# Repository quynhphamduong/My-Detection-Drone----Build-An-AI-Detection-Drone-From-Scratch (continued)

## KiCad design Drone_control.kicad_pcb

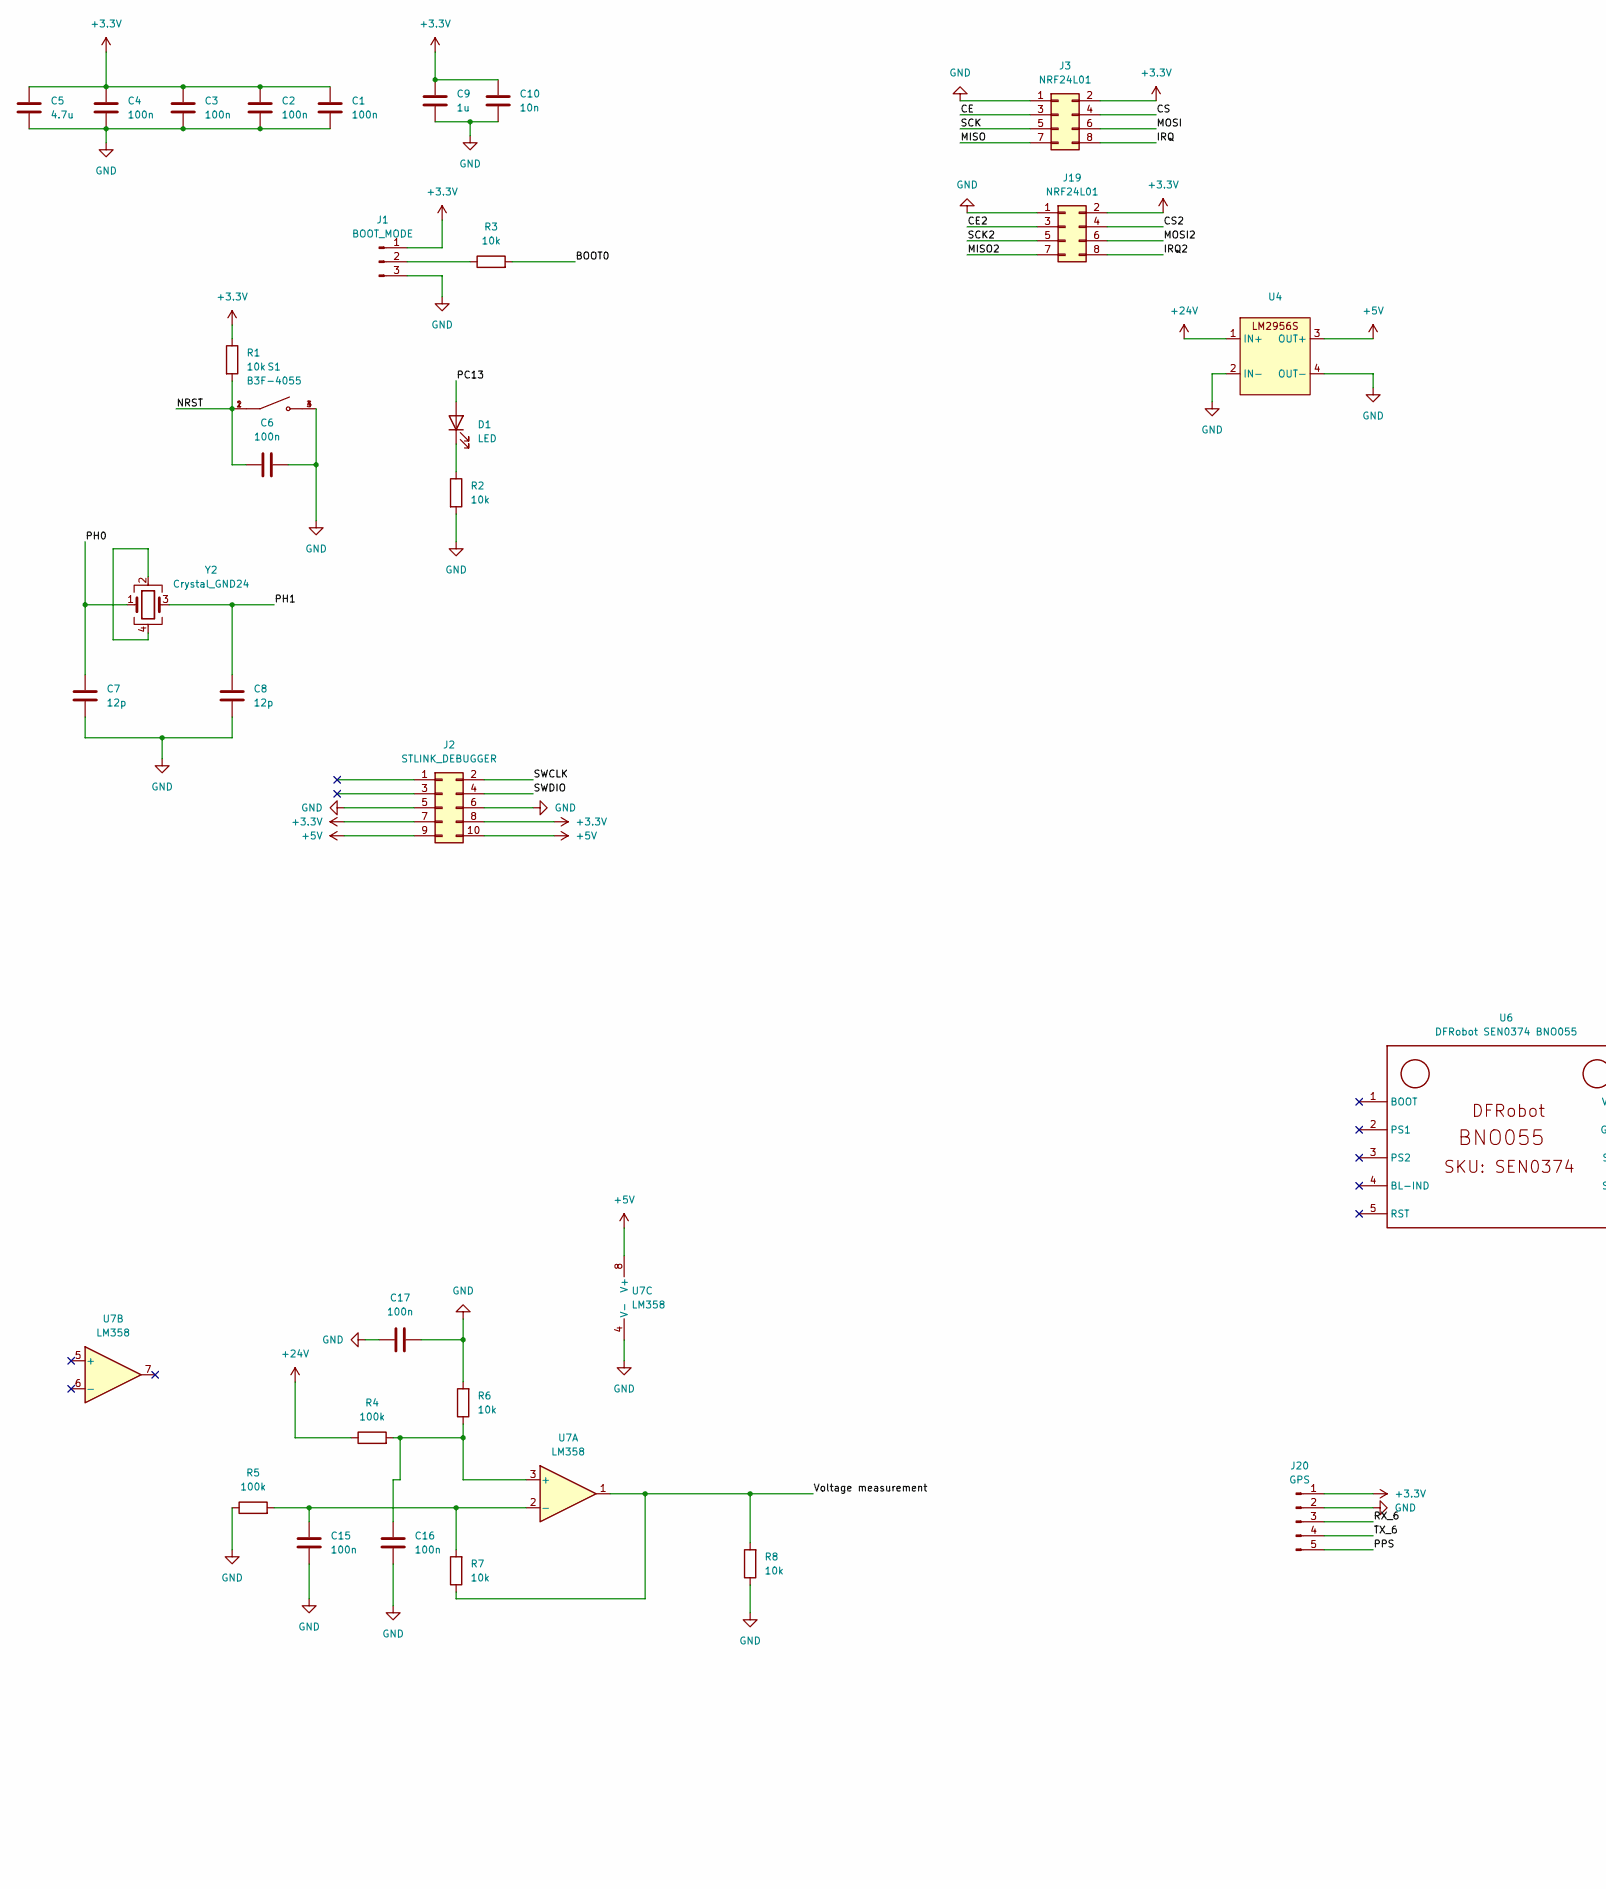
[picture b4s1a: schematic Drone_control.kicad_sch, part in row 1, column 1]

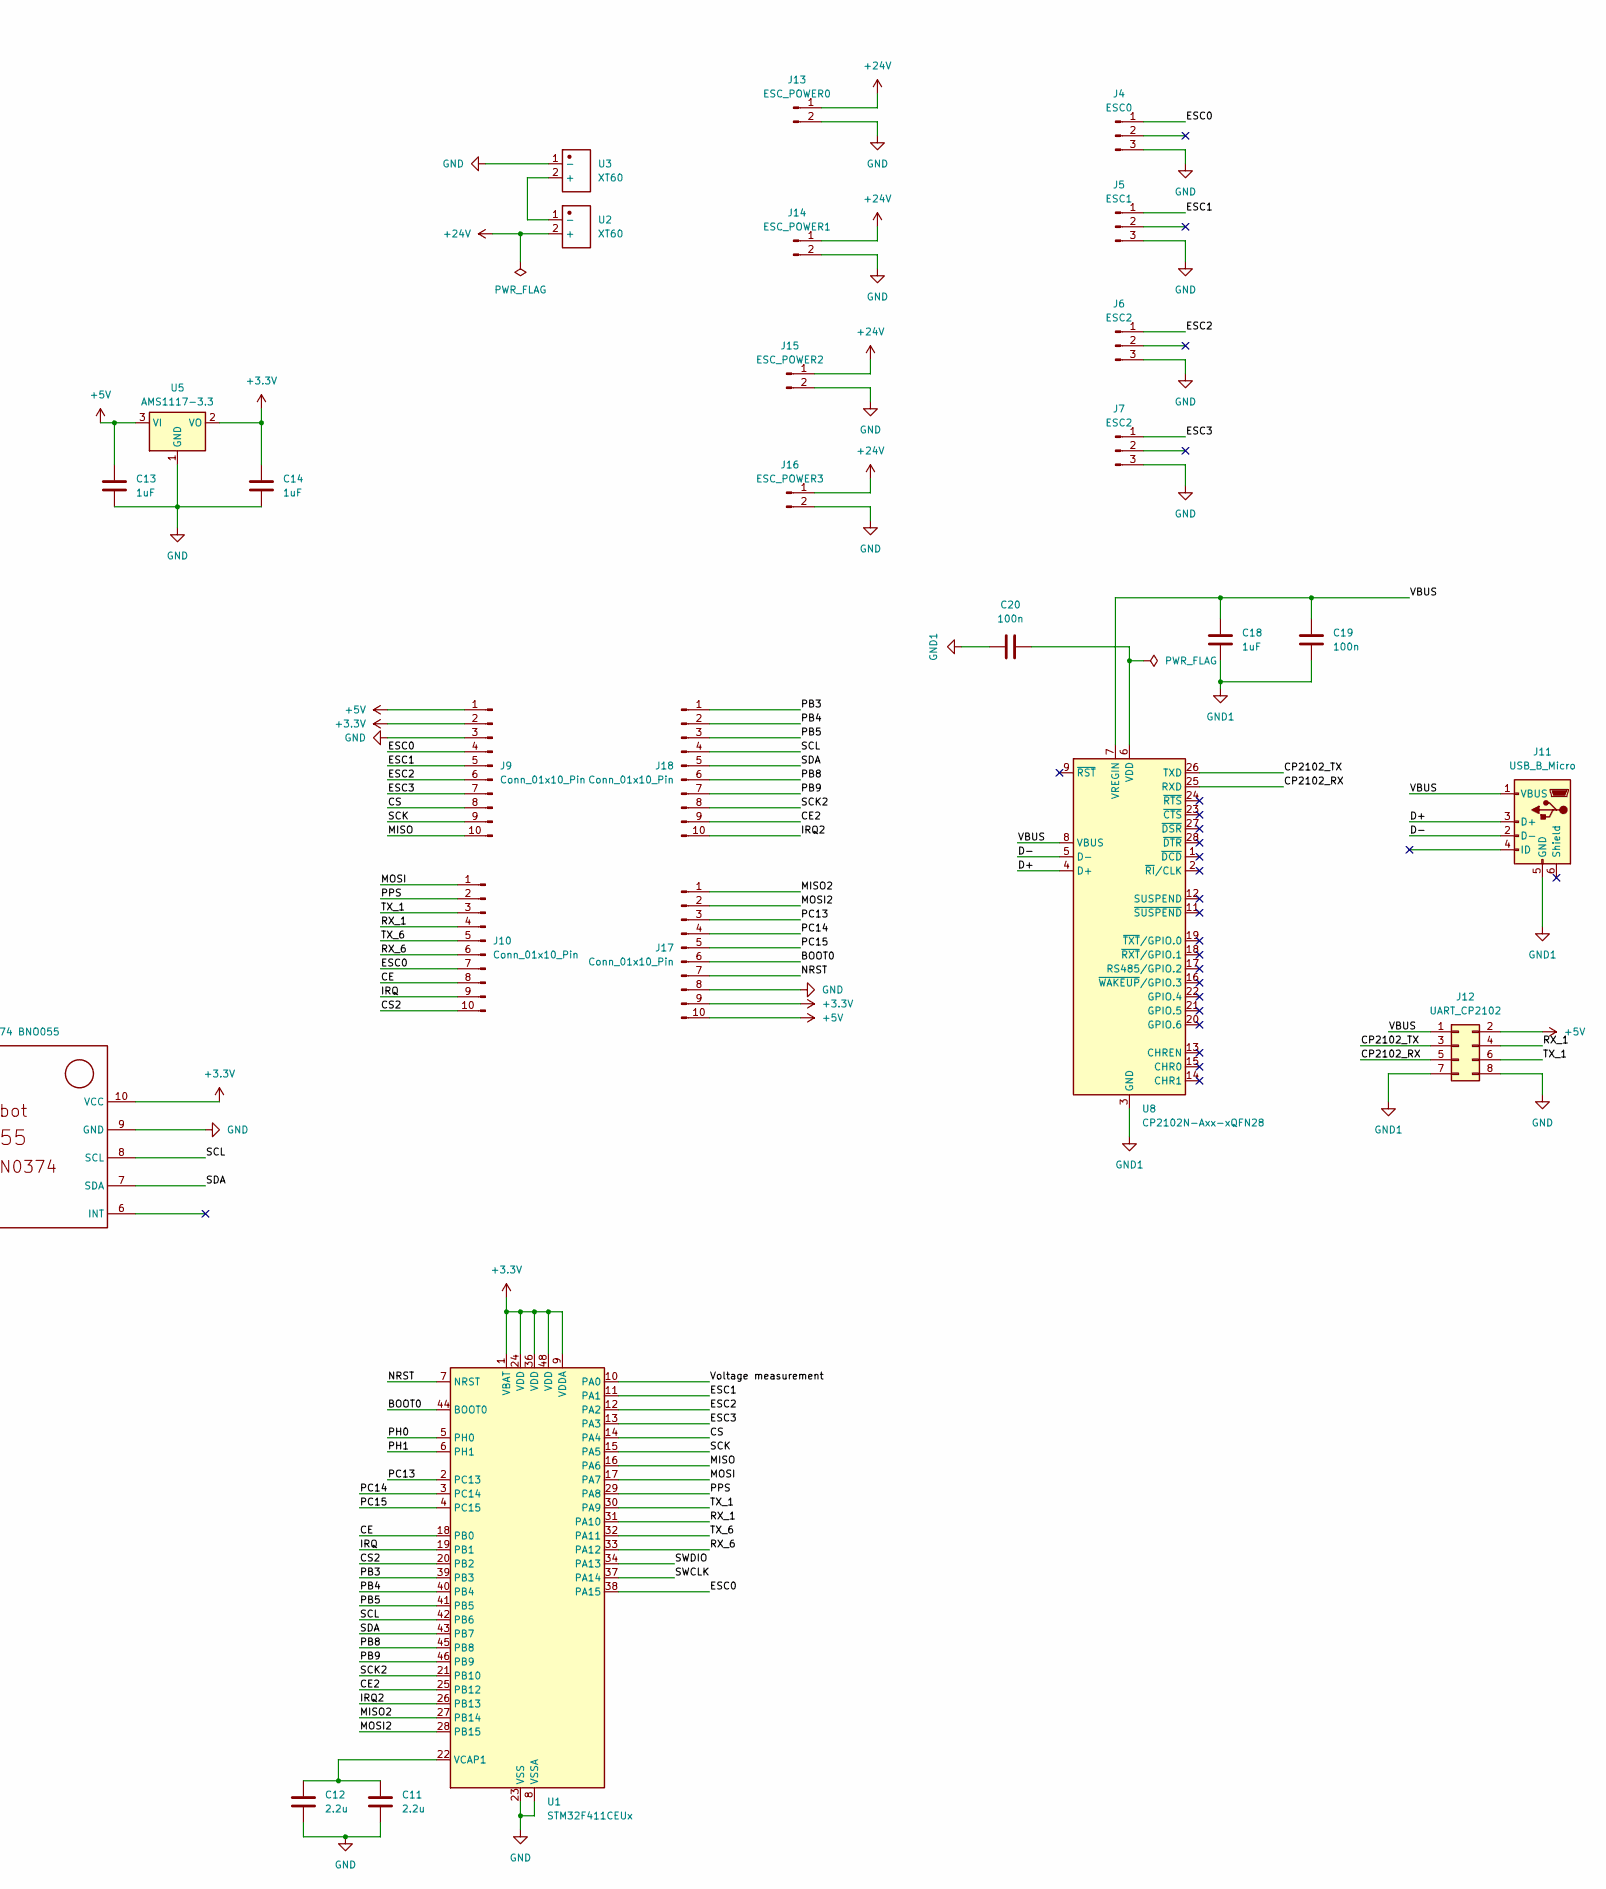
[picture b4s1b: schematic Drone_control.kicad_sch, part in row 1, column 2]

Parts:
C1, C2, C3, C4, C6, C15, C16, C17, C19, C20: 100n; C_0805_2012Metric_Pad1.18x1.45mm_HandSolder
C5: 4.7u; C_0805_2012Metric_Pad1.18x1.45mm_HandSolder
C7, C8: 12p; C_0805_2012Metric_Pad1.18x1.45mm_HandSolder
C9: 1u; C_0805_2012Metric_Pad1.18x1.45mm_HandSolder
C10: 10n; C_0805_2012Metric_Pad1.18x1.45mm_HandSolder
C11, C12: 2.2u; C_0805_2012Metric_Pad1.18x1.45mm_HandSolder
C13, C14, C18: 1uF; C_0805_2012Metric_Pad1.18x1.45mm_HandSolder
D1: LED; LED_0805_2012Metric_Pad1.15x1.40mm_HandSolder
J1: BOOT_MODE; PinHeader_1x03_P2.54mm_Vertical
J2: STLINK_DEBUGGER; IDC-Header_2x05_P2.54mm_Vertical
J3, J19: NRF24L01; PinHeader_2x04_P2.54mm_Vertical
J4: ESC0; PinHeader_1x03_P2.54mm_Vertical
J5: ESC1; PinHeader_1x03_P2.54mm_Vertical
J6, J7: ESC2; PinHeader_1x03_P2.54mm_Vertical
J9, J10, J17, J18: Conn_01x10_Pin; PinHeader_1x10_P2.54mm_Vertical
J11: USB_B_Micro; USB_Micro-B_Amphenol_10104110_Horizontal
J12: UART_CP2102; PinHeader_2x04_P2.54mm_Vertical
J13: ESC_POWER0; ESC_Power_Pad
J14: ESC_POWER1; ESC_Power_Pad
J15: ESC_POWER2; ESC_Power_Pad
J16: ESC_POWER3; ESC_Power_Pad
J20: GPS; PinHeader_1x05_P2.54mm_Vertical
R1, R2, R3, R6, R7, R8: 10k; R_0805_2012Metric_Pad1.20x1.40mm_HandSolder
R4, R5: 100k; R_0805_2012Metric_Pad1.20x1.40mm_HandSolder
S1: B3F-4055; SW_B3F-4055; PARTREV A070-E1-08
U1: STM32F411CEUx; QFN-48-1EP_7x7mm_P0.5mm_EP5.6x5.6mm
U2, U3: XT60; AMASS_XT60-M_1x02_P7.20mm_Vertical; Manufacturer Part XT60
U4: LM2596_Module
U5: AMS1117-3.3; SOT-223-3_TabPin2
U6: DFRobot SEN0374 BNO055; FOOTPRINT DFROBOT SEN0374 BNO055
U7: LM358; DIP-8_W7.62mm_Socket
U8: CP2102N-Axx-xQFN28; QFN-28-1EP_5x5mm_P0.5mm_EP3.35x3.35mm
Y2: Crystal_GND24; Crystal_SMD_5032-4Pin_5.0x3.2mm

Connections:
+3.3V: C1.1, C2.1, C3.1, C4.1, C5.1, C9.1, C10.1, C14.2, J1.1, J2.7, J2.8, J3.2, J9.2, J17.9, J19.2, J20.1, R1.1, U1.1 (VBAT), U1.9 (VDDA), U1.24 (VDD), U1.36 (VDD), U1.48 (VDD), U5.2 (VO), U6.10 (VCC)
+5V: C13.2, J2.9, J2.10, J9.1, J12.2, J17.10, U4.3 (OUT+), U5.3 (VI), U7.8 (V+)
+24V: J13.1, J14.1, J15.1, J16.1, R4.1, U2.2 (+), U4.1 (IN+)
/BOOT0: J17.6, R3.2, U1.44 (BOOT0)
/CE: J3.3, J10.8, U1.18 (PB0)
/CE2: J18.9, J19.3, U1.25 (PB12)
/CP2102_RX: J12.5, U8.25 (RXD)
/CP2102_TX: J12.3, U8.26 (TXD)
/CS: J3.4, J9.8, U1.14 (PA4)
/CS2: J10.10, J19.4, U1.20 (PB2)
/D+: J11.3 (D+), U8.4 (D+)
/D-: J11.2 (D-), U8.5 (D-)
/ESC0: J4.1, J9.4, J10.7, U1.38 (PA15)
/ESC1: J5.1, J9.5, U1.11 (PA1)
/ESC2: J6.1, J9.6, U1.12 (PA2)
/ESC3: J7.1, J9.7, U1.13 (PA3)
/IRQ: J3.8, J10.9, U1.19 (PB1)
/IRQ2: J18.10, J19.8, U1.26 (PB13)
/MISO: J3.7, J9.10, U1.16 (PA6)
/MISO2: J17.1, J19.7, U1.27 (PB14)
/MOSI: J3.6, J10.1, U1.17 (PA7)
/MOSI2: J17.2, J19.6, U1.28 (PB15)
/NRST: C6.1, J17.7, R1.2, S1.1, S1.2, U1.7 (NRST)
/PB3: J18.1, U1.39 (PB3)
/PB4: J18.2, U1.40 (PB4)
/PB5: J18.3, U1.41 (PB5)
/PB8: J18.6, U1.45 (PB8)
/PB9: J18.7, U1.46 (PB9)
/PC13: D1.2 (A), J17.3, U1.2 (PC13)
/PC14: J17.4, U1.3 (PC14)
/PC15: J17.5, U1.4 (PC15)
/PH0: C7.2, U1.5 (PH0), Y2.1
/PH1: C8.2, U1.6 (PH1), Y2.3
/PPS: J10.2, J20.5, U1.29 (PA8)
/RX_1: J10.4, J12.4, U1.31 (PA10)
/RX_6: J10.6, J20.3, U1.33 (PA12)
/SCK: J3.5, J9.9, U1.15 (PA5)
/SCK2: J18.8, J19.5, U1.21 (PB10)
/SCL: J18.4, U1.42 (PB6), U6.8 (SCL)
/SDA: J18.5, U1.43 (PB7), U6.7 (SDA)
/SWCLK: J2.2, U1.37 (PA14)
/SWDIO: J2.4, U1.34 (PA13)
/TX_1: J10.3, J12.6, U1.30 (PA9)
/TX_6: J10.5, J20.4, U1.32 (PA11)
/VBUS: C18.2, C19.1, J11.1 (VBUS), J12.1, U8.7 (VREGIN), U8.8 (VBUS)
/Voltage measurement: R7.1, R8.2, U1.10 (PA0), U7.1
GND: C1.2, C2.2, C3.2, C4.2, C5.2, C6.2, C7.1, C8.1, C9.2, C10.2, C11.2, C12.2, C13.1, C14.1, C15.2, C16.2, C17.1, C17.2, J1.3, J2.5, J2.6, J3.1, J4.3, J5.3, J6.3, J7.3, J9.3, J12.8, J13.2, J14.2, J15.2, J16.2, J17.8, J19.1, J20.2, R2.2, R5.1, R6.2, R8.1, S1.3, S1.4, U1.8 (VSSA), U1.23 (VSS), U1.35 (VSS), U1.47 (VSS), U1.49 (VSS), U3.1 (-), U4.2 (IN-), U4.4 (OUT-), U5.1 (GND), U6.9 (GND), U7.4 (V-)
GND1: C18.1, C19.2, C20.2, J11.5 (GND), J12.7, U8.3 (GND), U8.29 (GND)
unnamed: D1.1 (K), R2.1
unnamed: J1.2, R3.1
unnamed: C11.1, C12.1, U1.22 (VCAP1)
unnamed: U2.1 (-), U3.2 (+)
unnamed: C16.1, R4.2, R6.1, U7.3 (+)
unnamed: C15.1, R5.2, R7.2, U7.2 (-)
unnamed: C20.1, U8.6 (VDD)
unnamed: Y2.2, Y2.4

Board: 2 copper layers, 58 parts (0 on the bottom side), 56 nets, no tracks yet.

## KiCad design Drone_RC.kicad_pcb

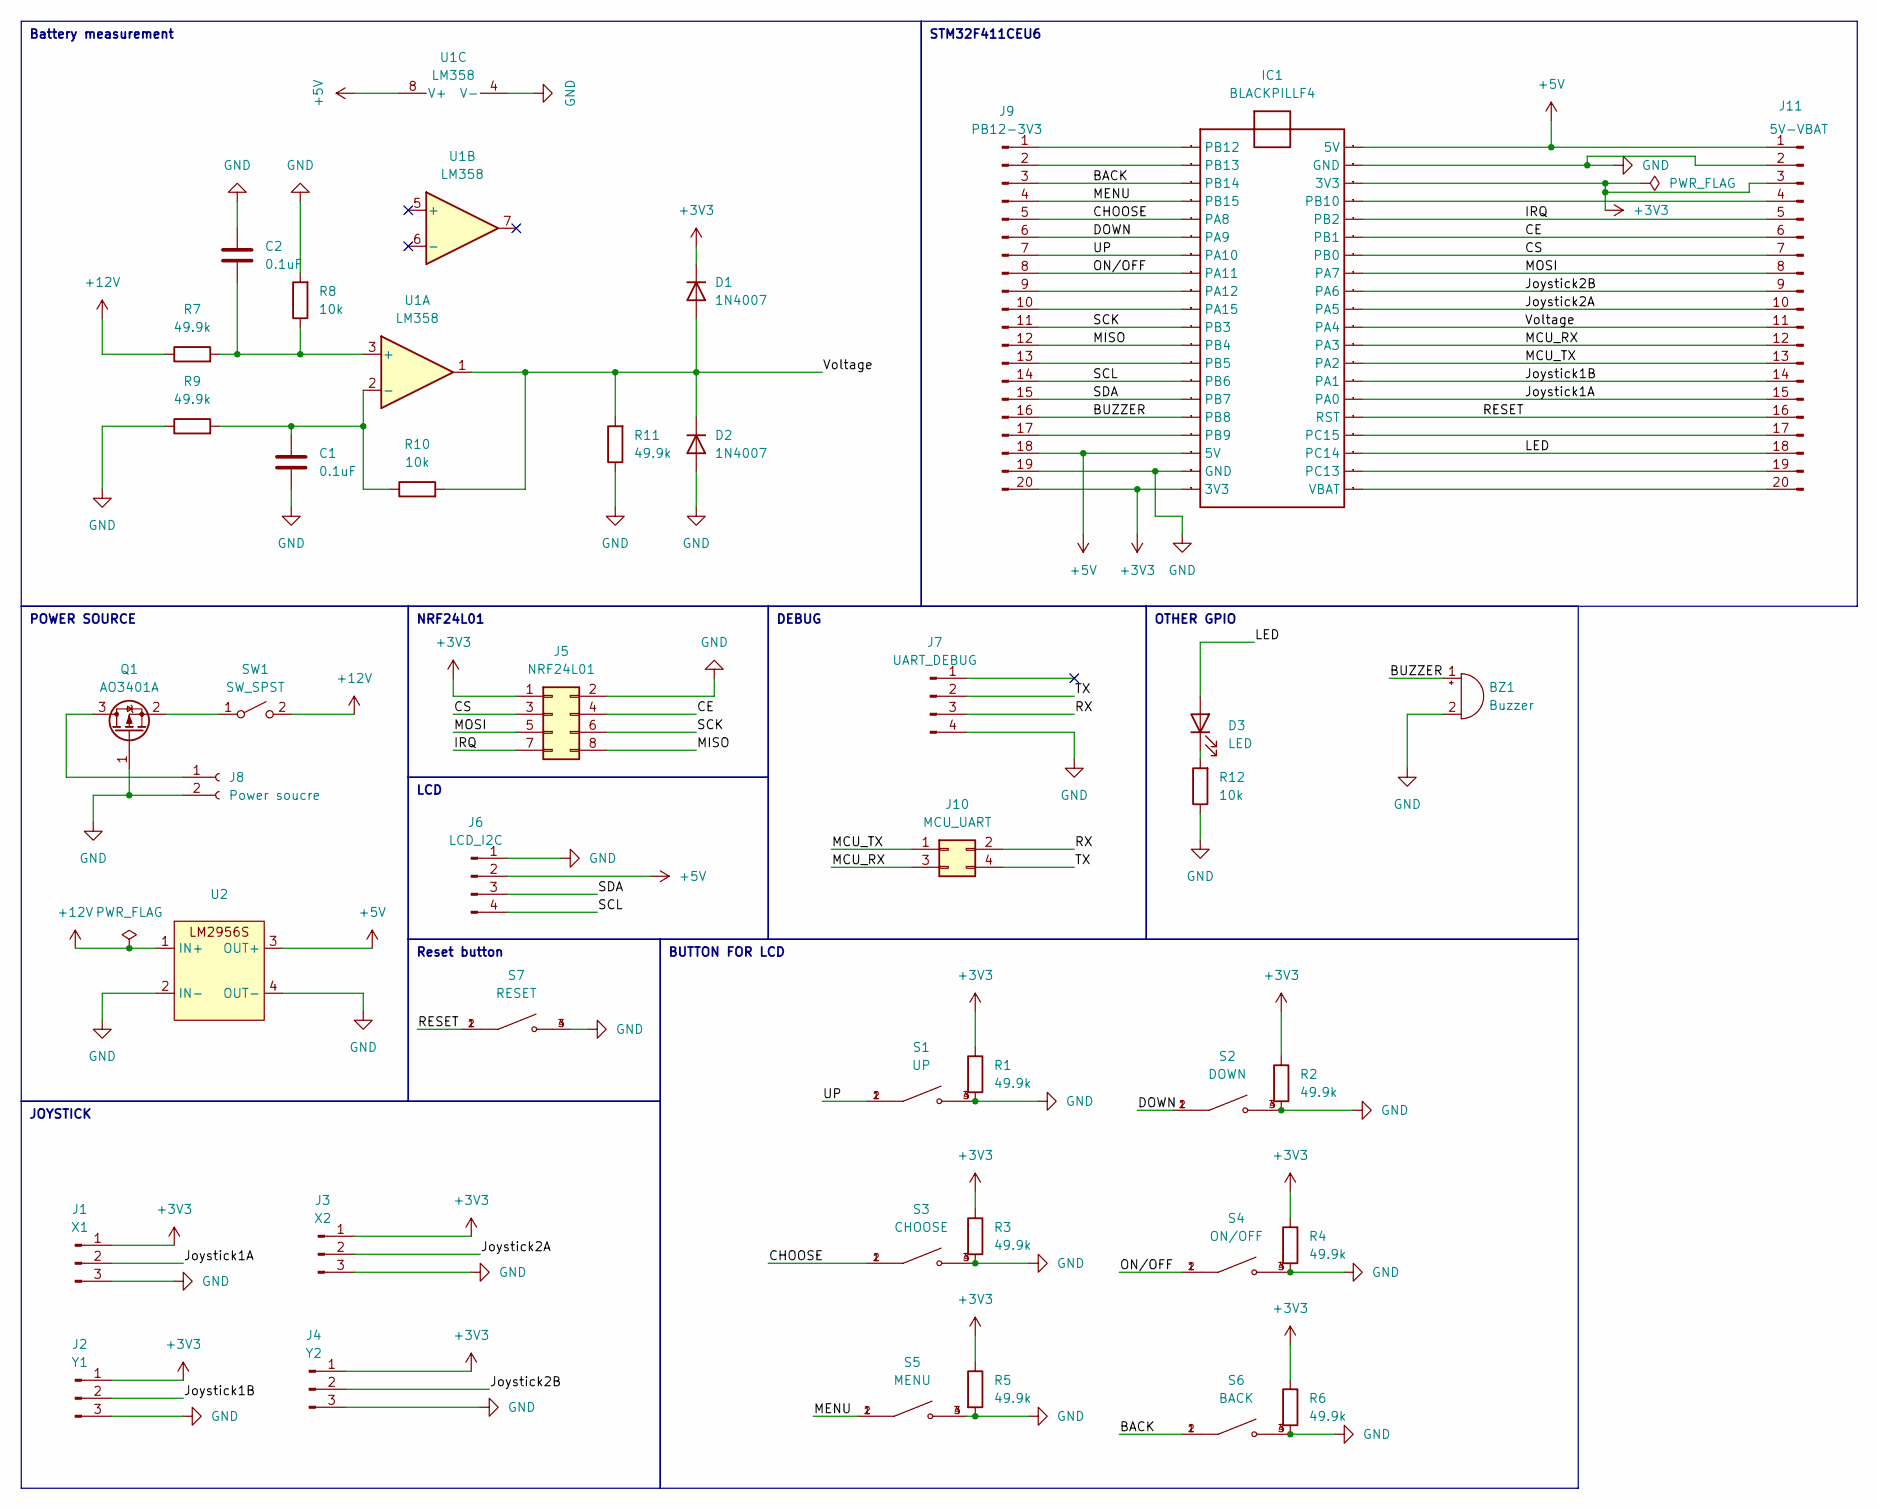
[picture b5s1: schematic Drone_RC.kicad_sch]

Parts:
BZ1: Buzzer; Buzzer_12x9.5RM7.6
C1, C2: 0.1uF; C_0805_2012Metric_Pad1.18x1.45mm_HandSolder
D1, D2: 1N4007; D_DO-41_SOD81_P10.16mm_Horizontal
D3: LED; LED_D3.0mm
IC1: BLACKPILLF4; Manufacturer Part BlackPill
J1: X1; PinHeader_1x03_P2.54mm_Vertical
J2: Y1; PinHeader_1x03_P2.54mm_Vertical
J3: X2; PinHeader_1x03_P2.54mm_Vertical
J4: Y2; PinHeader_1x03_P2.54mm_Vertical
J5: NRF24L01; PinSocket_2x04_P2.54mm_Vertical
J6: LCD_I2C; PinHeader_1x04_P2.54mm_Vertical
J7: UART_DEBUG; PinHeader_1x04_P2.54mm_Vertical
J8: Power soucre; Samtec_HPM-02-01-x-S_Straight_1x02_Pitch5.08mm
J9: PB12-3V3; PinHeader_1x20_P2.54mm_Vertical
J10: MCU_UART; PinHeader_2x02_P2.54mm_Vertical
J11: 5V-VBAT; PinHeader_1x20_P2.54mm_Vertical
Q1: AO3401A; SOT-23
R1, R2, R3, R4, R5, R6, R7, R9, R11: 49.9k; R_0805_2012Metric_Pad1.20x1.40mm_HandSolder
R8, R10, R12: 10k; R_0805_2012Metric_Pad1.20x1.40mm_HandSolder
S1: UP; SW_B3F-4055; PARTREV A070-E1-08
S2: DOWN; SW_B3F-4055; PARTREV A070-E1-08
S3: CHOOSE; SW_B3F-4055; PARTREV A070-E1-08
S4: ON/OFF; SW_B3F-4055; PARTREV A070-E1-08
S5: MENU; SW_B3F-4055; PARTREV A070-E1-08
S6: BACK; SW_B3F-4055; PARTREV A070-E1-08
S7: RESET; SW_B3F-4055; PARTREV A070-E1-08
SW1: SW_SPST; Switch_6A_21x22x15custom
U1: LM358; DIP-8_W7.62mm_Socket
U2: LM2596_Module

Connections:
+3V3: D1.1 (K), IC1.3V3_1 (3V3), IC1.3V3_2 (3V3), J1.1, J2.1, J3.1, J4.1, J5.1, J9.20, J11.3, R1.1, R2.1, R3.1, R4.1, R5.1, R6.1
+5V: IC1.5V_1 (5V), IC1.5V_2 (5V), J6.2, J9.18, J11.1, U1.8 (V+), U2.3 (OUT+)
+12V: R7.1, SW1.2 (B), U2.1 (IN+)
/BACK: IC1.PB14, J9.3, S6.1, S6.2
/BUZZER: BZ1.1 (+), IC1.PB8, J9.16
/CE: IC1.PB1, J5.4, J11.6
/CHOOSE: IC1.PA8, J9.5, S3.1, S3.2
/CS: IC1.PB0, J5.3, J11.7
/DOWN: IC1.PA9, J9.6, S2.1, S2.2
/IRQ: IC1.PB2, J5.7, J11.5
/Joystick1A: IC1.PA0, J1.2, J11.15
/Joystick1B: IC1.PA1, J2.2, J11.14
/Joystick2A: IC1.PA5, J3.2, J11.10
/Joystick2B: IC1.PA6, J4.2, J11.9
/LED: D3.2 (A), IC1.PC14, J11.18
/MCU_RX: IC1.PA3, J10.3, J11.12
/MCU_TX: IC1.PA2, J10.1, J11.13
/MENU: IC1.PB15, J9.4, S5.1, S5.2
/MISO: IC1.PB4, J5.8, J9.12
/MOSI: IC1.PA7, J5.5, J11.8
/ON/OFF: IC1.PA11, J9.8, S4.1, S4.2
/RESET: IC1.RST, J11.16, S7.1, S7.2
/RX: J7.3, J10.2
/SCK: IC1.PB3, J5.6, J9.11
/SCL: IC1.PB6, J6.4, J9.14
/SDA: IC1.PB7, J6.3, J9.15
/TX: J7.2, J10.4
/UP: IC1.PA10, J9.7, S1.1, S1.2
/Voltage: D1.2 (A), D2.1 (K), IC1.PA4, J11.11, R10.2, R11.2, U1.1
GND: BZ1.2 (-), C1.2, C2.1, D2.2 (A), IC1.GND_1 (GND), IC1.GND_3 (GND), J1.3, J2.3, J3.3, J4.3, J5.2, J6.1, J7.4, J8.2, J9.19, J11.2, Q1.1 (G), R1.2, R2.2, R3.2, R4.2, R5.2, R6.2, R8.2, R9.1, R11.1, R12.1, S1.3, S1.4, S2.3, S2.4, S3.3, S3.4, S4.3, S4.4, S5.3, S5.4, S6.3, S6.4, S7.3, S7.4, U1.4 (V-), U2.2 (IN-), U2.4 (OUT-)
unnamed: D3.1 (K), R12.2
unnamed: J8.1, Q1.3 (D)
unnamed: IC1.PB12, J9.1
unnamed: IC1.PB13, J9.2
unnamed: IC1.PA12, J9.9
unnamed: IC1.PA15, J9.10
unnamed: IC1.PB5, J9.13
unnamed: IC1.PB9, J9.17
unnamed: IC1.PB10, J11.4
unnamed: IC1.PC15, J11.17
unnamed: IC1.PC13, J11.19
unnamed: IC1.VBAT, J11.20
unnamed: Q1.2 (S), SW1.1 (A)
unnamed: C2.2, R7.2, R8.1, U1.3 (+)
unnamed: C1.1, R9.2, R10.1, U1.2 (-)

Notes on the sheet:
NRF24L01
STM32F411CEU6
JOYSTICK
Battery measurement
DEBUG
LCD
BUTTON FOR LCD
Reset button
POWER SOURCE
OTHER GPIO

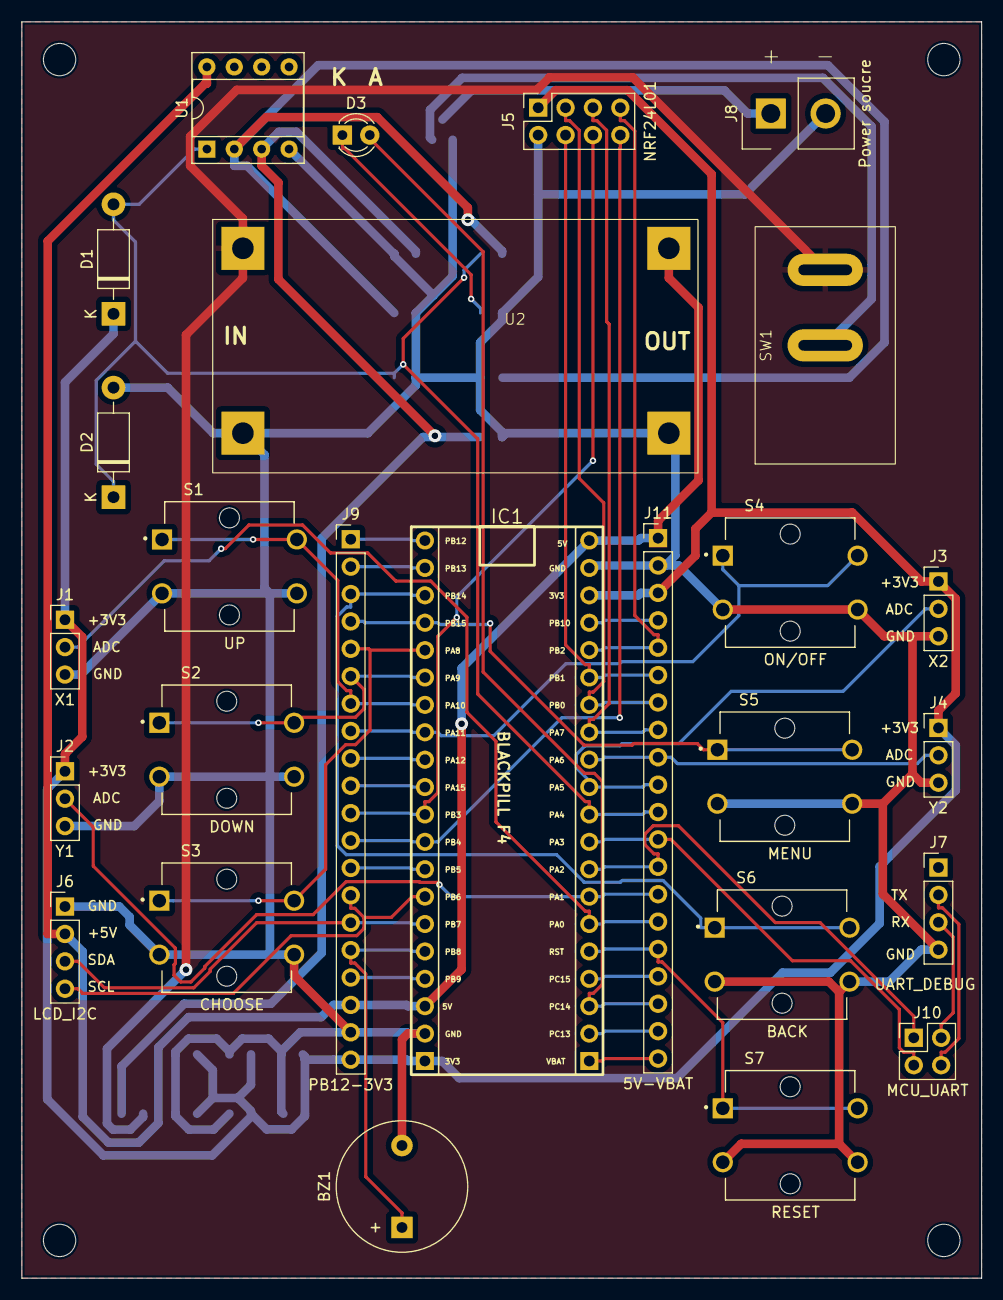
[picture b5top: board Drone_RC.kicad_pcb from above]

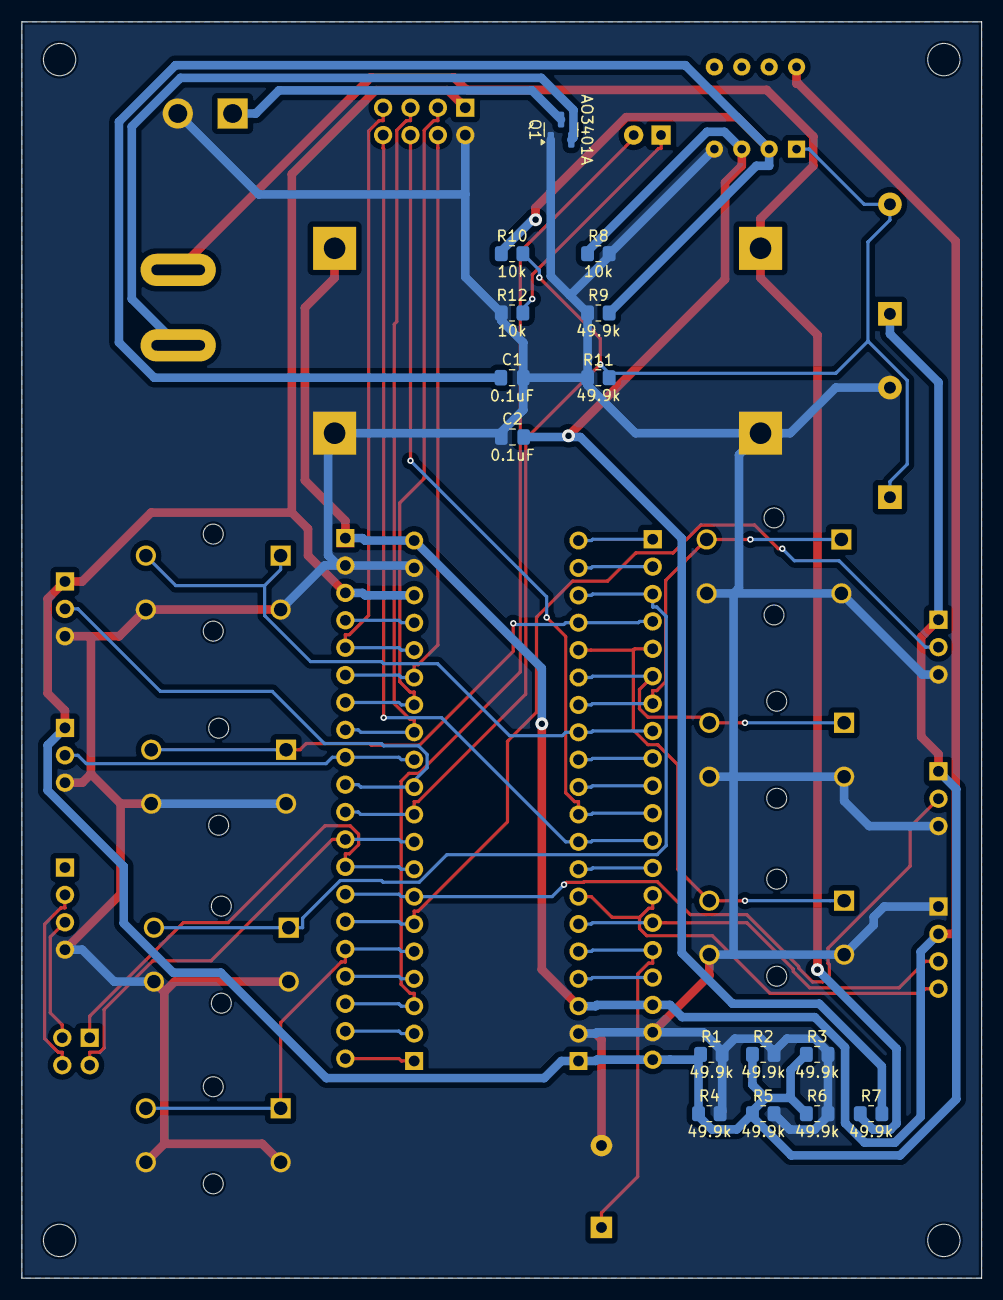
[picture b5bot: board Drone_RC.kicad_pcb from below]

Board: 2 copper layers, 89.0 x 116.5 mm, 41 parts (15 on the bottom side), 45 nets.

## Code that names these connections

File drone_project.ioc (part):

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Mcu.Name=STM32F411C(C-E)Ux
Mcu.Package=UFQFPN48
Mcu.UserName=STM32F411CEUx
PA0-WKUP.Signal=ADCx_IN0
PA1.Signal=S_TIM2_CH2
PA10.Mode=Asynchronous
PA10.Signal=USART1_RX
PA11.Mode=Asynchronous
PA11.Signal=USART6_TX
PA12.Mode=Asynchronous
PA12.Signal=USART6_RX
PA13.Mode=Serial_Wire
PA13.Signal=SYS_JTMS-SWDIO
PA14.Mode=Serial_Wire
PA14.Signal=SYS_JTCK-SWCLK
PA15.Signal=S_TIM2_CH1_ETR
PA2.Signal=S_TIM2_CH3
PA3.Signal=S_TIM2_CH4
PA4.GPIOParameters=GPIO_Label
PA4.GPIO_Label=CS1
PA4.Signal=GPIO_Output
PA5.Mode=Full_Duplex_Master
PA5.Signal=SPI1_SCK
PA6.Mode=Full_Duplex_Master
PA6.Signal=SPI1_MISO
PA7.Mode=Full_Duplex_Master
PA7.Signal=SPI1_MOSI
PA8.GPIOParameters=GPIO_Label
PA8.GPIO_Label=PPS
PA8.Signal=GPIO_Input
PA9.Mode=Asynchronous
PA9.Signal=USART1_TX
PB0.GPIOParameters=GPIO_Label
PB0.GPIO_Label=CE1
PB0.Signal=GPIO_Output
PB1.GPIOParameters=GPIO_Label
PB1.GPIO_Label=IRQ1
PB1.Signal=GPIO_Input
PB10.Mode=Full_Duplex_Master
PB10.Signal=SPI2_SCK
PB12.GPIOParameters=GPIO_Label
PB12.GPIO_Label=CE2
PB12.Signal=GPIO_Output
PB13.GPIOParameters=GPIO_Label
PB13.GPIO_Label=IRQ2
PB13.Signal=GPIO_Input
PB14.Mode=Full_Duplex_Master
PB14.Signal=SPI2_MISO
PB15.Mode=Full_Duplex_Master
PB15.Signal=SPI2_MOSI
PB2.GPIOParameters=GPIO_Label
PB2.GPIO_Label=CS2
PB2.Signal=GPIO_Output
PB6.Mode=I2C
PB6.Signal=I2C1_SCL
PB7.Mode=I2C
PB7.Signal=I2C1_SDA
PC13-ANTI_TAMP.GPIOParameters=GPIO_PuPd,GPIO_ModeDefaultOutputPP
PC13-ANTI_TAMP.GPIO_ModeDefaultOutputPP=GPIO_MODE_OUTPUT_PP
PC13-ANTI_TAMP.GPIO_PuPd=GPIO_NOPULL
PC13-ANTI_TAMP.Signal=GPIO_Output
PH0\ -\ OSC_IN.Mode=HSE-External-Oscillator
PH0\ -\ OSC_IN.Signal=RCC_OSC_IN
PH1\ -\ OSC_OUT.Mode=HSE-External-Oscillator
PH1\ -\ OSC_OUT.Signal=RCC_OSC_OUT
RCC.HSE_VALUE=25000000
RCC.SYSCLKFreq_VALUE=84000000
RCC.SYSCLKSource=RCC_SYSCLKSOURCE_PLLCLK
board=custom

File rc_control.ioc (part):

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Mcu.Name=STM32F411C(C-E)Ux
Mcu.Package=UFQFPN48
Mcu.UserName=STM32F411CEUx
PA0-WKUP.Signal=ADCx_IN0
PA1.Signal=ADCx_IN1
PA10.GPIOParameters=GPIO_PuPd,GPIO_Label
PA10.GPIO_Label=UP
PA10.GPIO_PuPd=GPIO_PULLUP
PA10.Signal=GPXTI10
PA11.Mode=Asynchronous
PA11.Signal=USART6_TX
PA12.Mode=Asynchronous
PA12.Signal=USART6_RX
PA13.Mode=Serial_Wire
PA13.Signal=SYS_JTMS-SWDIO
PA14.Mode=Serial_Wire
PA14.Signal=SYS_JTCK-SWCLK
PA15.Mode=Asynchronous
PA15.Signal=USART1_TX
PA2.Signal=ADCx_IN2
PA3.Signal=ADCx_IN3
PA4.Signal=ADCx_IN4
PA5.Mode=Full_Duplex_Master
PA5.Signal=SPI1_SCK
PA6.Mode=Full_Duplex_Master
PA6.Signal=SPI1_MISO
PA7.Mode=Full_Duplex_Master
PA7.Signal=SPI1_MOSI
PA8.GPIOParameters=GPIO_PuPd,GPIO_Label
PA8.GPIO_Label=SELECT
PA8.GPIO_PuPd=GPIO_PULLUP
PA8.Signal=GPXTI8
PA9.GPIOParameters=GPIO_PuPd,GPIO_Label
PA9.GPIO_Label=DOWN
PA9.GPIO_PuPd=GPIO_PULLUP
PA9.Signal=GPXTI9
PB0.GPIOParameters=GPIO_Label
PB0.GPIO_Label=CS
PB0.Signal=GPIO_Output
PB1.GPIOParameters=GPIO_Label
PB1.GPIO_Label=CE
PB1.Signal=GPIO_Output
PB14.GPIOParameters=GPIO_PuPd,GPIO_Label
PB14.GPIO_Label=HOME
PB14.GPIO_PuPd=GPIO_PULLUP
PB14.Signal=GPXTI14
PB15.GPIOParameters=GPIO_PuPd,GPIO_Label
PB15.GPIO_Label=BACK
PB15.GPIO_PuPd=GPIO_PULLUP
PB15.Signal=GPXTI15
PB2.GPIOParameters=GPIO_Label
PB2.GPIO_Label=IRQ
PB2.Signal=GPIO_Input
PB6.Mode=I2C
PB6.Signal=I2C1_SCL
PB7.Mode=Asynchronous
PB7.Signal=USART1_RX
PB8.GPIOParameters=GPIO_Label
PB8.GPIO_Label=BUZZER
PB8.Signal=GPIO_Output
PB9.Mode=I2C
PB9.Signal=I2C1_SDA
PC13-ANTI_TAMP.Signal=GPIO_Output
PH0\ -\ OSC_IN.Mode=HSE-External-Oscillator
PH0\ -\ OSC_IN.Signal=RCC_OSC_IN
PH1\ -\ OSC_OUT.Mode=HSE-External-Oscillator
PH1\ -\ OSC_OUT.Signal=RCC_OSC_OUT
RCC.HSE_VALUE=25000000
RCC.SYSCLKFreq_VALUE=84000000
RCC.SYSCLKSource=RCC_SYSCLKSOURCE_PLLCLK
board=custom

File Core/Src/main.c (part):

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  /*Configure GPIO pin Output Level */
  HAL_GPIO_WritePin(GPIOB, CS2_Pin|CE2_Pin, GPIO_PIN_RESET);

  /*Configure GPIO pin : PC13 */
  GPIO_InitStruct.Pin = GPIO_PIN_13;
  GPIO_InitStruct.Mode = GPIO_MODE_OUTPUT_PP;
  GPIO_InitStruct.Pull = GPIO_NOPULL;
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  GPIO_InitStruct.Speed = GPIO_SPEED_FREQ_LOW;
  HAL_GPIO_Init(GPIOB, &GPIO_InitStruct);

  /*Configure GPIO pin : IRQ2_Pin */
  GPIO_InitStruct.Pin = IRQ2_Pin;
  GPIO_InitStruct.Mode = GPIO_MODE_INPUT;
  GPIO_InitStruct.Pull = GPIO_PULLUP;
  HAL_GPIO_Init(IRQ2_GPIO_Port, &GPIO_InitStruct);

  /* USER CODE BEGIN MX_GPIO_Init_2 */

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				}
				for(int u=0;u<a;u++)
				{
					uart1_rx[u]=0;
				}
				goto reset;
			}
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				}
				for(int u=0;u<a;u++)
				{
					uart6_rx[u]=0;
				}
				goto Init_Interupt;
			}
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
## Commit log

2025-06-07 chore: create drone_project
2025-06-07 chore: add icm20602 and nrf library
2025-06-07 chore : update README.md
2025-06-24 chore: add PID, Drone_control
2025-06-27 feat: add lcdgui lib
2025-06-28 feat: two way nrf communication
2025-06-29 chore: change nrf
2025-06-29 two_way
2025-06-29 save
2025-06-29 successful pipe 0
2025-06-29 successful pipe 1
2025-06-30 wip: pack 2 two_way into function
2025-06-30 chore : update nrf two_way com
2025-06-30 fix: two_way_com
2025-07-01 Chore: Change nrf_lib at main
2025-07-01 wip:add lib rccommand
2025-07-02 wip: change rccommand lib
2025-07-04 wip: add adctask
2025-07-05 wip: fix rccommand lib and main.c
2025-07-05 stupid
2025-07-08 feat : RC_Circuit
2025-07-08 feat: Control circuit
2025-07-10 chore: fix nrf 1
2025-07-10 chore: fix nrf 2
2025-07-10 chore: fix nrf 3
2025-07-10 chore: fix nrf 4
2025-07-10 feat: add bno055
2025-07-10 chore : synchronize with main nrf
2025-07-13 Chore: fix nrf on rc_control01
2025-07-13 feat : bmp180
2025-07-26 chore: change pin
2025-08-02 chore : fix adc
2025-08-02 chore : fix command
2025-09-27 First push
2025-10-04 New version
2025-10-04 Hardware
2025-10-12 Feat: Self_tuning P controller
2025-11-09 multiple_feature
2025-11-10 First C TCP
2025-11-11 send to rasp
2025-11-16 add comment
2025-12-18 new feature
